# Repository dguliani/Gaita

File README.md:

# Gaita

## Development Process 
1. Create a new branch for your feature
2. Push commits
3. Open a PR (one per feature ideally)
4. As soon as a PR receives a +1, it can be merged into master.

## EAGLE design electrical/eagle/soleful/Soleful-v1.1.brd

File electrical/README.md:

# Gaita

## Electrical/Hardware Documentation

In order to be able to successfully use/change the schematics, ensure first that you have:

1. Installed Eagle
2. Cloned the repository to a local location

Having done those two things, there are a few modifications that may need to be made to ensure all the utlized libraries can be loaded on Eagle. First:

1. Open/Launch Eagle
2. Go to File -> Options -> Directories

You will notice that the paths for each of the various Eagle categories are set up here, for things like Libraries, Documentation, Design Rules and Projects. The two primary paths that will need modifications will be Libraries and Projects.

### Projects

Add the local path to the soleful directory in this repository by either appending the currently given path on Eagle with a colon (:) on Mac, or a semi-colon (;) on Windows. The resulting path may look like this:

`$EAGLEDIR/projects/examples:$HOME/<path-to-locally-cloned-git-repo>/eagle/soleful`

### Libraries

Similarly, this project uses the following Libraries:

1. SparkFun Eagle Libraries (https://github.com/sparkfun/SparkFun-Eagle-Libraries)
2. Pyboard Eagle (https://github.com/micropython/pyboard)
3. Adafruit BNO055 Library (https://github.com/adafruit/Adafruit-BNO055-Breakout-PCB)
4. Adafruit Eagle Library (https://github.com/adafruit/Adafruit-Eagle-Library)

Each of these libraries should be in the libraries folder of this repository, so append the path to each of these folders following a similar fashion as above in Eagle. An example is below:

`$EAGLEDIR/lbr:$HOME/<path-to-locally-cloned-git-repo>/eagle/libraries/SparkFun-Eagle-Libraries-master:<so on for each library>`

## Using Eagle

Follow the tutorials below to get a good sense of how to use Eagle, and it's various different functions.

1. Schematic (https://learn.sparkfun.com/tutorials/using-eagle-schematic)
2. Layout (https://learn.sparkfun.com/tutorials/using-eagle-board-layout)

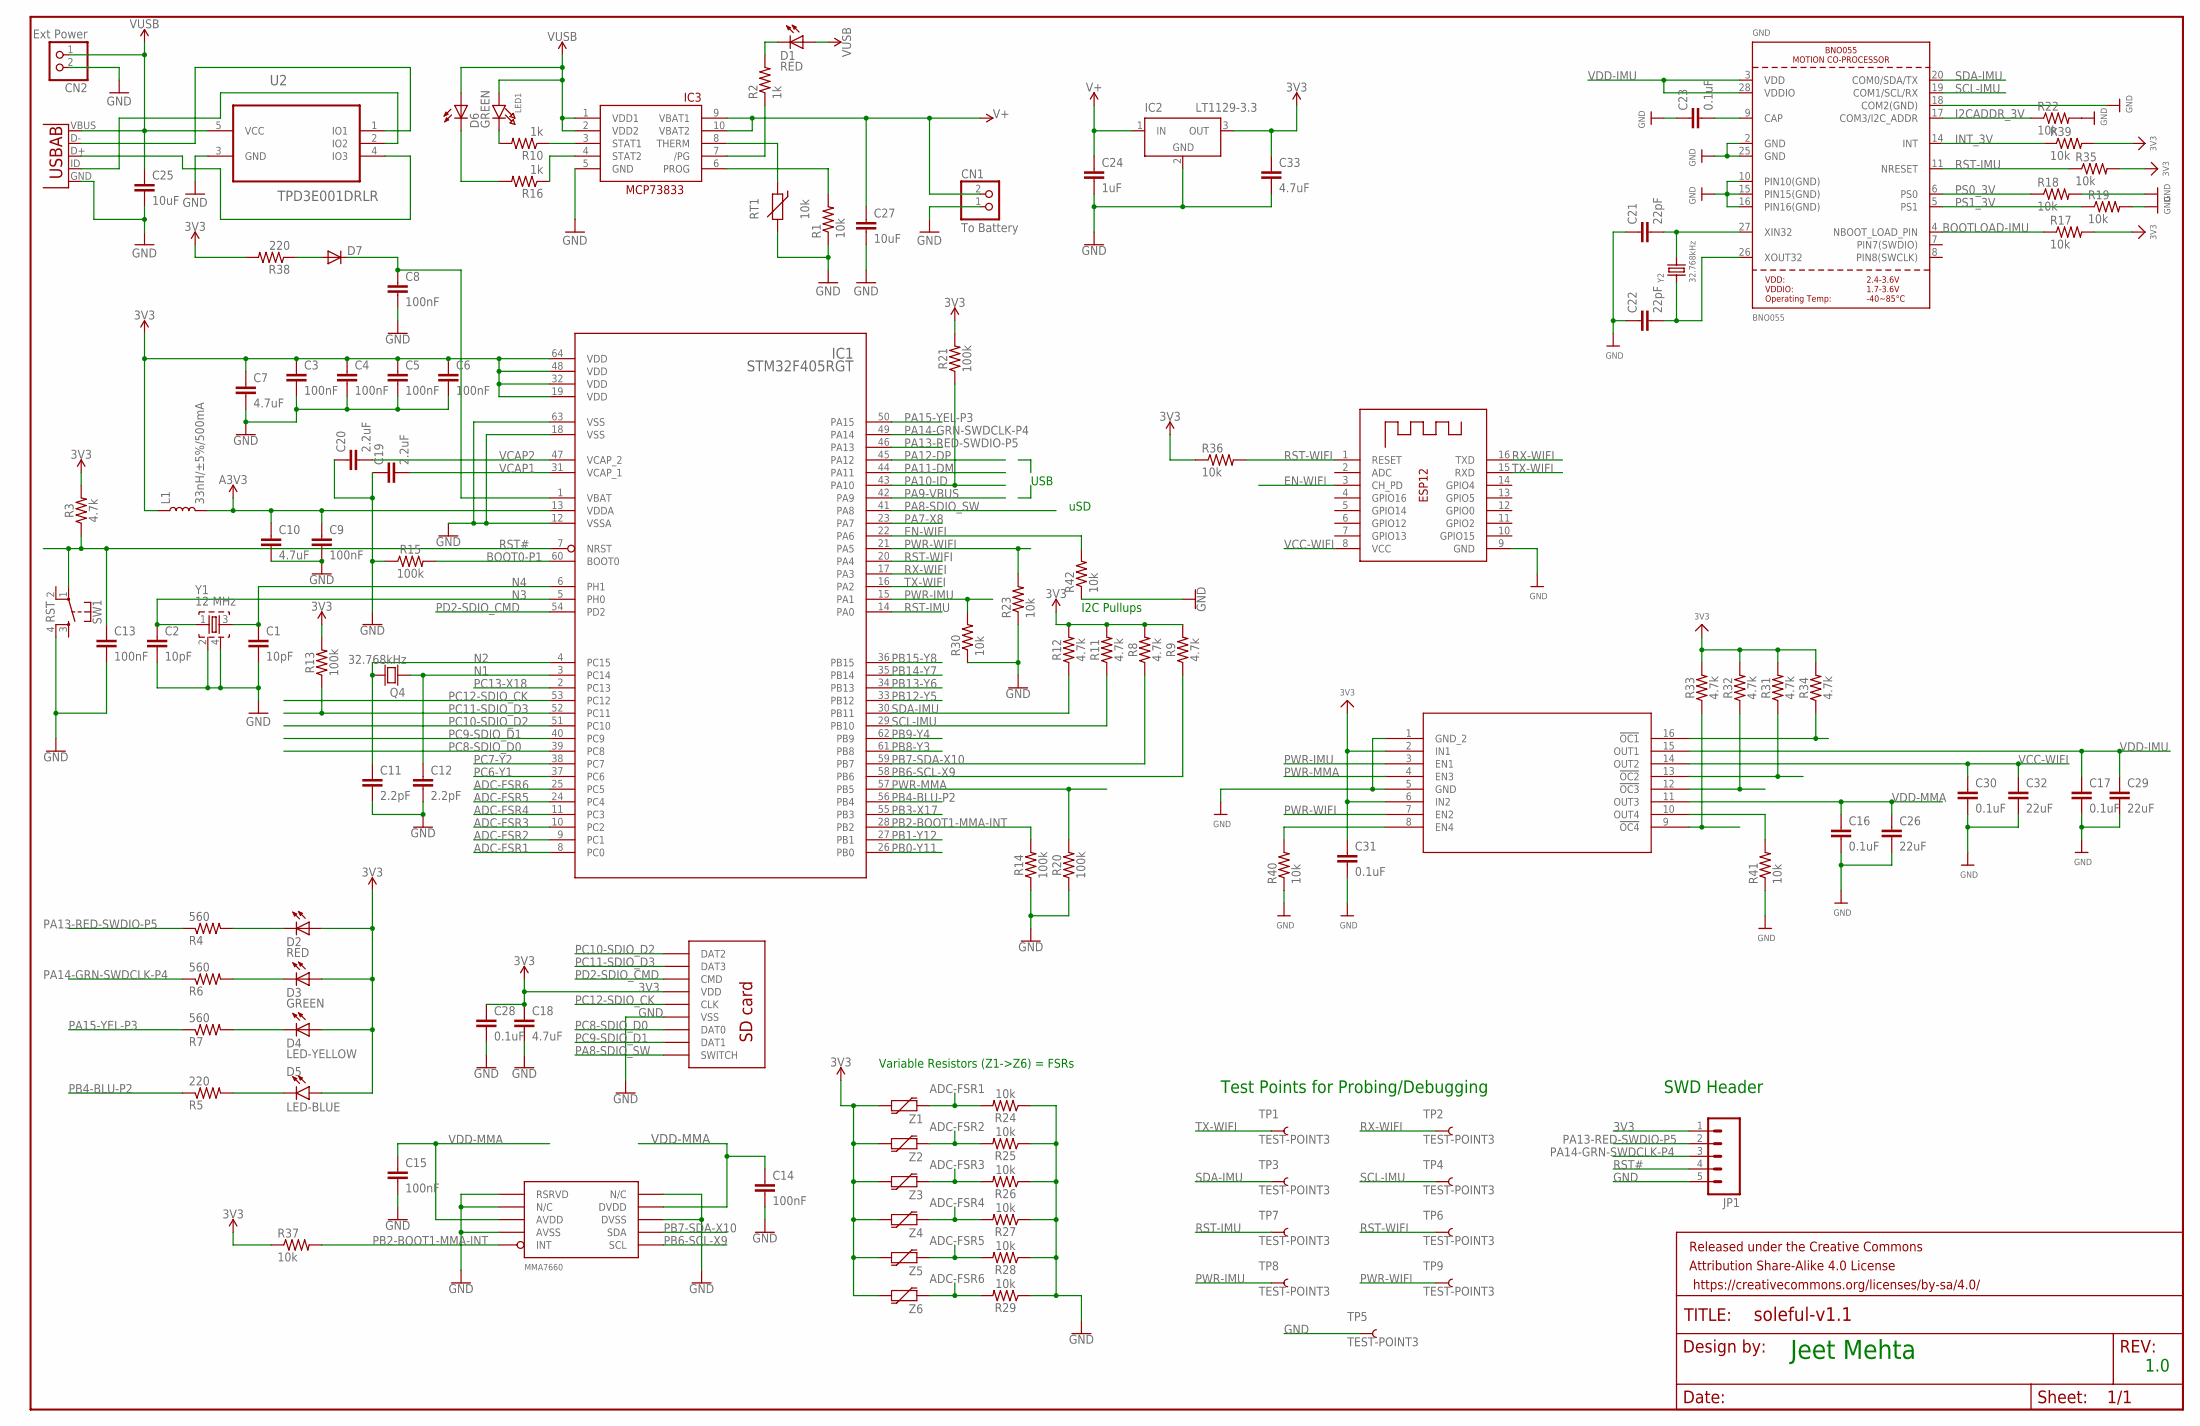
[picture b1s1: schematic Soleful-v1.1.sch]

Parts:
C1, C2: 10pF; 0603
C3, C4, C5, C6, C8, C9, C13, C14, C15: 100nF; 0603-CAP
C7, C10, C18: 4.7uF; 0603
C11, C12: 2.2pF; 0603-CAP
C16, C17, C28, C30: 0.1uF; 0402-CAP
C19, C20: 2.2uF; 0402-CAP
C21, C22: 22pF; 0603-CAP
C23, C31: 0.1uF; 0603-CAP
C24: 1uF; 0805
C25, C27: 10uF; 1206
C26, C29, C32: 22uF; 0805
C33: 4.7uF; 0402-CAP
CN1: To Battery; JST-PH-2-SMT
CN2: Ext Power; JST-PH-2-SMT
D1, D2: RED; LED-0603
D3, D6: GREEN; LED-0603
D4: LED-YELLOW; LED-0603
D5: LED-BLUE; LED-0603@1
D7: DIODESOT23; SOT23-3
FRAME1: FRAME-LEDGER; CREATIVE_COMMONS
GND: BNO055
IC1: STM32F405RGT; LQFP64
IC2: LT1129-3.3; SOT223
IC3: MCP73833-UN; MSOP10
JP1: M051.27MM; 1X05-1.27MM
L1: 33nH/±5%/500mA; 0603
LED1: LED0603; CHIPLED_0603
Q4: 32.768kHz; TXC-SMD-32X15
R1, R17, R18, R19, R22, R23, R30, R35, R36, R37, R39, R40, R41, R42: 10k; 0402-RES
R2, R10, R16: 1k; 0402-RES
R3, R8, R9, R11, R12, R31, R32, R33, R34: 4.7k; 0603
R4, R6, R7: 560; 0603-RES
R5, R38: 220; 0603-RES
R13, R14, R15, R20, R21: 100k; 0603
R24, R25, R26, R27, R28, R29: 10k; 0603
RT1: 10k; R-5
SW1: RST; TACTILE_SWITCH_SMD_4.6X2.8MM
TP1, TP2, TP3, TP4, TP5, TP6, TP7, TP8, TP9: TEST-POINT3; PAD.03X.03
U1: USB Power; USB-AB-MICRO-SMD
U2: TPD3E001DRLR; SOT50P160X60-5N
U$1: MMA7660; DFN10
U$9: MOLEX-SD-105027; MOLEX-SD-105027-PKG
U$18: TPS2054BDR; D16
X1: ESP-12
Y1: 12 MHz; FA-128
Y2: 32.768kHz; CRYSTAL_8X3.8
Z1, Z2, Z3, Z4, Z5, Z6: VARISTOR-0402; 0402-RES

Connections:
3V3: C3.1, C4.1, C5.1, C6.1, C7.1, C18.1, C28.1, C31.1, C33.1, D2.A, D3.A, D4.A, D5.A, IC1.19 (VDD), IC1.32 (VDD), IC1.48 (VDD), IC1.64 (VDD), IC2.3 (OUT), JP1.1, L1.1, R3.2, R8.2, R9.2, R11.2, R12.2, R13.2, R17.2, R21.2, R31.2, R32.2, R33.2, R34.2, R35.2, R36.1, R37.1, R38.2, R39.2, U$9.P$4 (VDD), U$18.2 (IN1), U$18.6 (IN2), Z1.2, Z2.2, Z3.2, Z4.2, Z5.2, Z6.2
A3V3: C9.1, C10.1, IC1.13 (VDDA), L1.2
ADC-FSR1: IC1.8 (PC0), R24.2, Z1.1
ADC-FSR2: IC1.9 (PC1), R25.2, Z2.1
ADC-FSR3: IC1.10 (PC2), R26.2, Z3.1
ADC-FSR4: IC1.11 (PC3), R27.2, Z4.1
ADC-FSR5: IC1.24 (PC4), R28.2, Z5.1
ADC-FSR6: IC1.25 (PC5), R29.2, Z6.1
BOOT0-P1: IC1.60 (BOOT0), R15.2
BOOTLOAD-IMU: GND.4 (NBOOT_LOAD_PIN), R17.1
EN-WIFI: IC1.22 (PA6), R42.2, X1.3 (CH_PD)
GND: C1.2, C2.2, C3.2, C4.2, C5.2, C6.2, C7.2, C8.2, C9.2, C10.2, C11.2, C12.2, C13.2, C14.2, C15.2, C16.2, C17.2, C18.2, C19.1, C20.1, C21.1, C22.1, C23.1, C24.2, C25.2, C26.2, C27.2, C28.2, C29.2, C30.2, C31.2, C32.2, C33.2, CN1.1 (2), CN2.2 (1), GND.2 (GND), GND.10 (PIN10(GND)), GND.15 (PIN15(GND)), GND.16 (PIN16(GND)), GND.18 (COM2(GND)), GND.25 (GND), IC1.12 (VSSA), IC1.18 (VSS), IC1.63 (VSS), IC2.2 (GND), IC2.4 (GND), IC3.5 (GND), JP1.5, R1.1, R14.1, R15.1, R18.2, R19.2, R20.1, R22.2, R23.1, R24.1, R25.1, R26.1, R27.1, R28.1, R29.1, R30.1, R40.1, R41.1, R42.1, RT1.2, SW1.4, TP5.P$1, U1.GND, U2.3 (GND), U$1.P$1 (RSRVD), U$1.P$2 (N/C), U$1.P$4 (AVSS), U$1.P$8 (DVSS), U$1.P$10 (N/C), U$9.P$6 (VSS), U$18.1 (GND_2), U$18.5 (GND), X1.9 (GND), Y1.2, Y1.4
I2CADDR_3V: GND.17 (COM3/I2C_ADDR), R22.1
INT_3V: GND.14 (INT), R39.1
N1: C12.1, IC1.3 (PC14), Q4.P$1
N2: C11.1, IC1.4 (PC15), Q4.P$2
N3: C2.1, IC1.5 (PH0), Y1.1
N4: C1.1, IC1.6 (PH1), Y1.3
unnamed: D2.C, R4.2
unnamed: D3.C, R6.2
unnamed: D4.C, R7.2
unnamed: D5.C, R5.2
unnamed: D7.1 (A), R38.1
unnamed: IC3.6 (PROG), R1.2
unnamed: IC3.7 (/PG), R2.1
unnamed: D1.C, R2.2
unnamed: IC3.8 (THERM), RT1.1
unnamed: IC3.3 (STAT1), R10.1
unnamed: IC3.4 (STAT2), R16.1
unnamed: D6.C, R16.2
unnamed: LED1.C, R10.2
unnamed: R41.2, U$18.10 (OUT4)
unnamed: R34.1, U$18.16 (!OC1)
unnamed: R31.1, U$18.13 (!OC2)
unnamed: R32.1, U$18.12 (!OC3)
unnamed: R33.1, U$18.9 (!OC4)
unnamed: R40.2, U$18.8 (EN4)
unnamed: U1.D-, U2.1 (IO1)
unnamed: U1.D+, U2.4 (IO3)
unnamed: U1.ID (USBID), U2.2 (IO2)
unnamed: C21.2, GND.27 (XIN32), Y2.P$4 (2)
unnamed: C22.2, GND.26 (XOUT32), Y2.P$1 (1)
unnamed: C23.2, GND.9 (CAP)
PA7-X8: IC1.23 (PA7)
PA8-SDIO_SW: IC1.41 (PA8), U$9.G$1 (SWITCH)
PA9-VBUS: IC1.42 (PA9)
PA10-ID: IC1.43 (PA10), R21.1
PA11-DM: IC1.44 (PA11)
PA12-DP: IC1.45 (PA12)
PA13-RED-SWDIO-P5: IC1.46 (PA13), JP1.2, R4.1
PA14-GRN-SWDCLK-P4: IC1.49 (PA14), JP1.3, R6.1
PA15-YEL-P3: IC1.50 (PA15), R7.1
PB0-Y11: IC1.26 (PB0)
PB1-Y12: IC1.27 (PB1)
PB2-BOOT1-MMA-INT: IC1.28 (PB2), R14.2, R37.2, U$1.P$5 (INT)
PB3-X17: IC1.55 (PB3)
PB4-BLU-P2: IC1.56 (PB4), R5.1
PB6-SCL-X9: IC1.58 (PB6), R9.1, U$1.P$6 (SCL)
PB7-SDA-X10: IC1.59 (PB7), R8.1, U$1.P$7 (SDA)
PB8-Y3: IC1.61 (PB8)
PB9-Y4: IC1.62 (PB9)
PB12-Y5: IC1.33 (PB12)
PB13-Y6: IC1.34 (PB13)
PB14-Y7: IC1.35 (PB14)
PB15-Y8: IC1.36 (PB15)
PC6-Y1: IC1.37 (PC6)
PC7-Y2: IC1.38 (PC7)
PC8-SDIO_D0: IC1.39 (PC8), U$9.P$7 (DAT0)
PC9-SDIO_D1: IC1.40 (PC9), U$9.P$8 (DAT1)
PC10-SDIO_D2: IC1.51 (PC10), U$9.P$1 (DAT2)
PC11-SDIO_D3: IC1.52 (PC11), R13.1, U$9.P$2 (DAT3)
PC12-SDIO_CK: IC1.53 (PC12), U$9.P$5 (CLK)
PC13-X18: IC1.2 (PC13)
PD2-SDIO_CMD: IC1.54 (PD2), U$9.P$3 (CMD)
PS0_3V: GND.6 (PS0), R18.1
PS1_3V: GND.5 (PS1), R19.1
PWR-IMU: IC1.15 (PA1), R30.2, TP8.P$1, U$18.3 (EN1)
PWR-MMA: IC1.57 (PB5), R20.2, U$18.4 (EN3)
PWR-WIFI: IC1.21 (PA5), R23.2, TP9.P$1, U$18.7 (EN2)
RST#: C13.1, IC1.7 (NRST), JP1.4, R3.1, SW1.1
RST-IMU: GND.11 (NRESET), IC1.14 (PA0), R35.1, TP7.P$1
RST-WIFI: IC1.20 (PA4), R36.2, TP6.P$1, X1.1 (RESET)
RX-WIFI: IC1.17 (PA3), TP2.P$1, X1.16 (TXD)
SCL-IMU: GND.19 (COM1/SCL/RX), IC1.29 (PB10), R11.1, TP4.P$1
SDA-IMU: GND.20 (COM0/SDA/TX), IC1.30 (PB11), R12.1, TP3.P$1
TX-WIFI: IC1.16 (PA2), TP1.P$1, X1.15 (RXD)
V+: C24.1, C27.1, CN1.2 (1), IC2.1 (IN), IC3.9 (VBAT1), IC3.10 (VBAT2)
VBACKUP: C8.1, D7.3 (C), IC1.1 (VBAT)
VCAP1: C19.2, IC1.31 (VCAP_1)
VCAP2: C20.2, IC1.47 (VCAP_2)
VCC-WIFI: C30.1, C32.1, U$18.14 (OUT2), X1.8 (VCC)
VDD-IMU: C17.1, C29.1, GND.3 (VDD), GND.28 (VDDIO), U$18.15 (OUT1)
VDD-MMA: C14.1, C15.1, C16.1, C26.1, U$1.P$3 (AVDD), U$1.P$9 (DVDD), U$18.11 (OUT3)
VUSB: C25.1, CN2.1 (2), D1.A, D6.A, IC3.1 (VDD1), IC3.2 (VDD2), LED1.A, U1.VBUS, U2.5 (VCC)

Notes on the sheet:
uSD
USB
I2C Pullups
Jeet Mehta
1.0
Variable Resistors (Z1->Z6) = FSRs
Test Points for Probing/Debugging
SWD Header

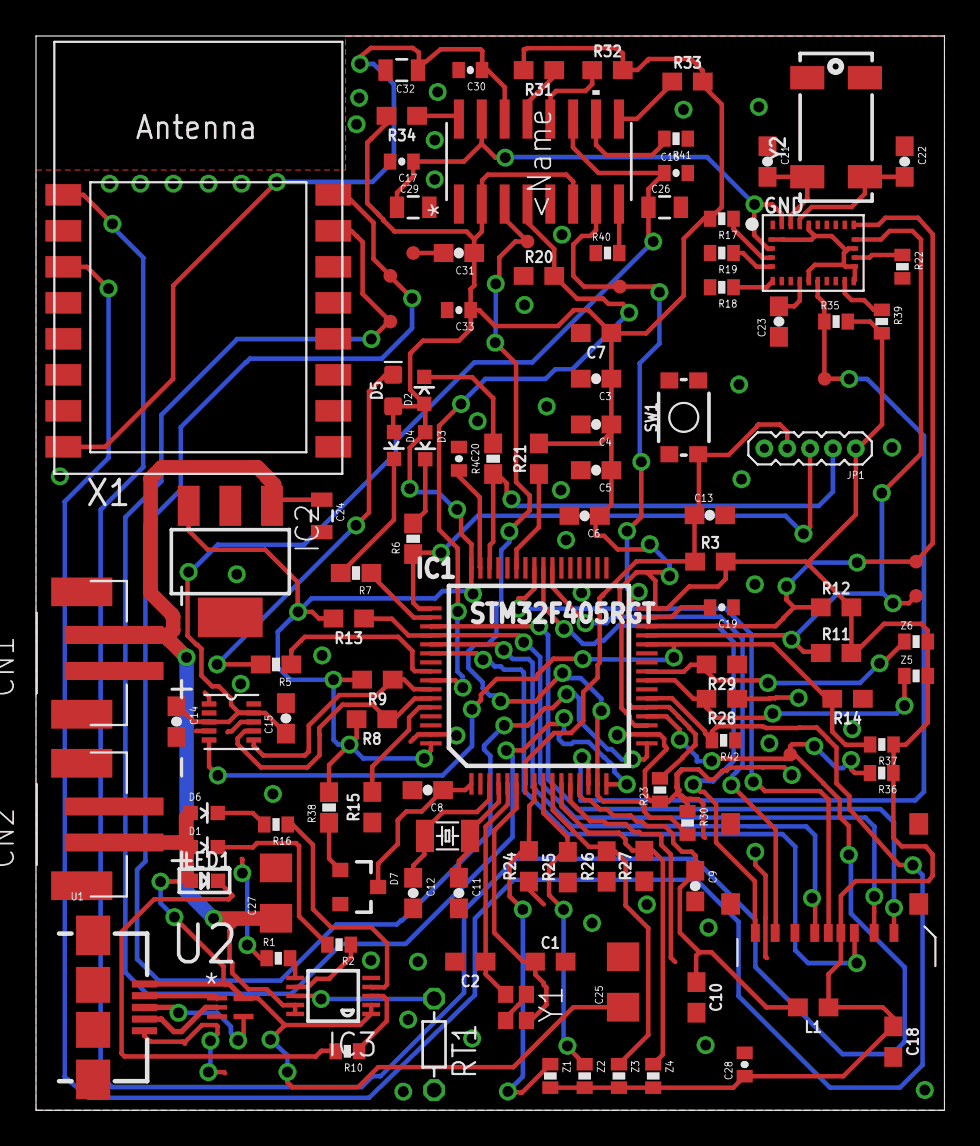
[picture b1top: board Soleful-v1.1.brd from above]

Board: 2 copper layers, 50.5 x 59.7 mm, 118 parts (0 on the bottom side), 78 nets.

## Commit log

2016-11-06 Initial file for grabbing accelerometer data from pyboard
2016-11-14 IMU driver working; next get calibration across boots
2016-11-20 Playing around with getting the imu to better recognize positional changes
2016-11-20 Small cleanup
2016-11-20 More cleanup
2016-12-06 Adding untested driver for wifi
2016-12-06 WIFI prototyping
2017-01-20 Modularization and measurement files
2017-01-20 Adding electrical side to version control
2017-01-20 Added documentation on running eagle
2017-01-20 further doc work
2017-01-20 code snippet
2017-01-20 minor change
2017-01-21 Work on schematic, starting from scratch due to lack of updated pyboard eagle files
2017-01-21 Finished IC-related wiring
2017-01-21 Further schematic work
2017-01-22 further work
2017-01-22 More work
2017-01-22 Trying to ignore save files
2017-01-22 still trying to get rid of save files
2017-01-22 Finally worked
2017-01-22 Added IMU files
2017-01-23 Finished IMU, added FSRs
2017-01-23 Added LiPo charging IC, need to wire it together
2017-01-23 Removed power switches and stuff until flow is determined
2017-01-23 Cleanup for collab
2017-01-23 Adding to cleanup
2017-01-24 Some changes
2017-01-24 Adding FSR Sampling for first fsr
2017-01-24 Current working file for pyboard sensor tests
2017-01-24 All parts connected
2017-01-25 Added test points and replaced old components with proper ones
2017-01-25 Final push for schematic, basic set up is complete
2017-01-25 Added FETs for power cycling
2017-01-29 added initial board file
2017-02-02 Fist commit towards v1 demo
2017-02-06 Adding revision 1.1
2017-02-07 added v1.1 schematic and board files which include new changes
2017-02-08 finished board layout bitch
2017-02-09 fixed all DRC issues
2017-02-10 added new components to schematic
2017-02-10 finished the entire layout based on Sunstones DRC rules bitches
2017-03-02 Getting ready for fydp demo
2017-03-03 setting up infrastructure for visualizations
2017-03-12 Bringing in working wifi and improving driver
2017-03-14 Visualizations and wifi progress
2017-03-15 Adding postprocessing code to parse process steps and extract gait factors
2017-03-16 updated plots and data
2017-03-16 Updating tokens
2017-03-16 added some new foot thing
2017-03-17 Demo Finalized
2017-03-20 Raw data

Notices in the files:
parts and their libraries:
SparkFun-Capacitors: Licensing: Creative Commons ShareAlike 4.0 International - https://creativecommons.org/licenses/by-sa/4.0
SparkFun-Aesthetics: Released under the Creative Commons Attribution Share-Alike 4.0 License
SparkFun-Aesthetics: https://creativecommons.org/licenses/by-sa/4.0
